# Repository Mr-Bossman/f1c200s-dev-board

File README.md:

"# f1c200s-dev-board usb otg needs to be fixed and sdcard locaton and flash pad size and 3.3 requlators pad is rotated"

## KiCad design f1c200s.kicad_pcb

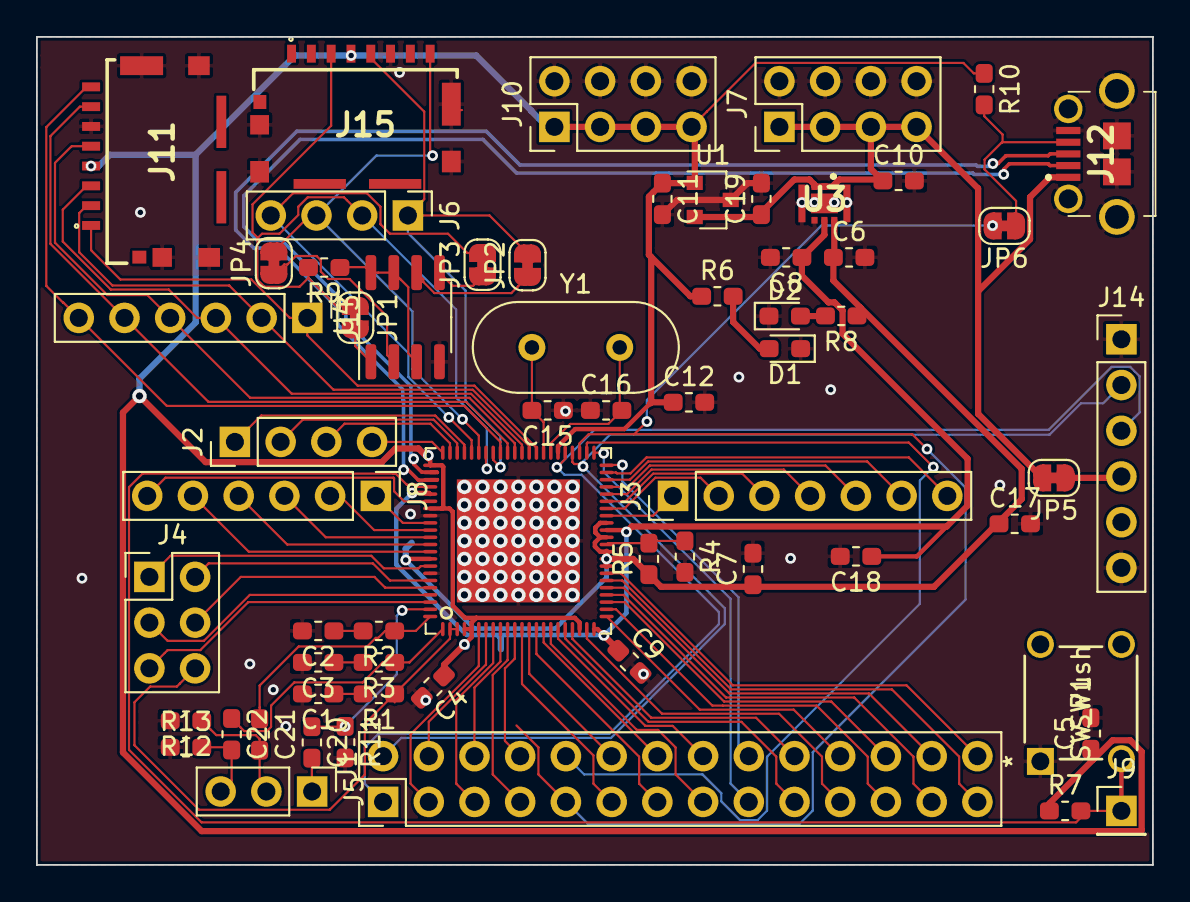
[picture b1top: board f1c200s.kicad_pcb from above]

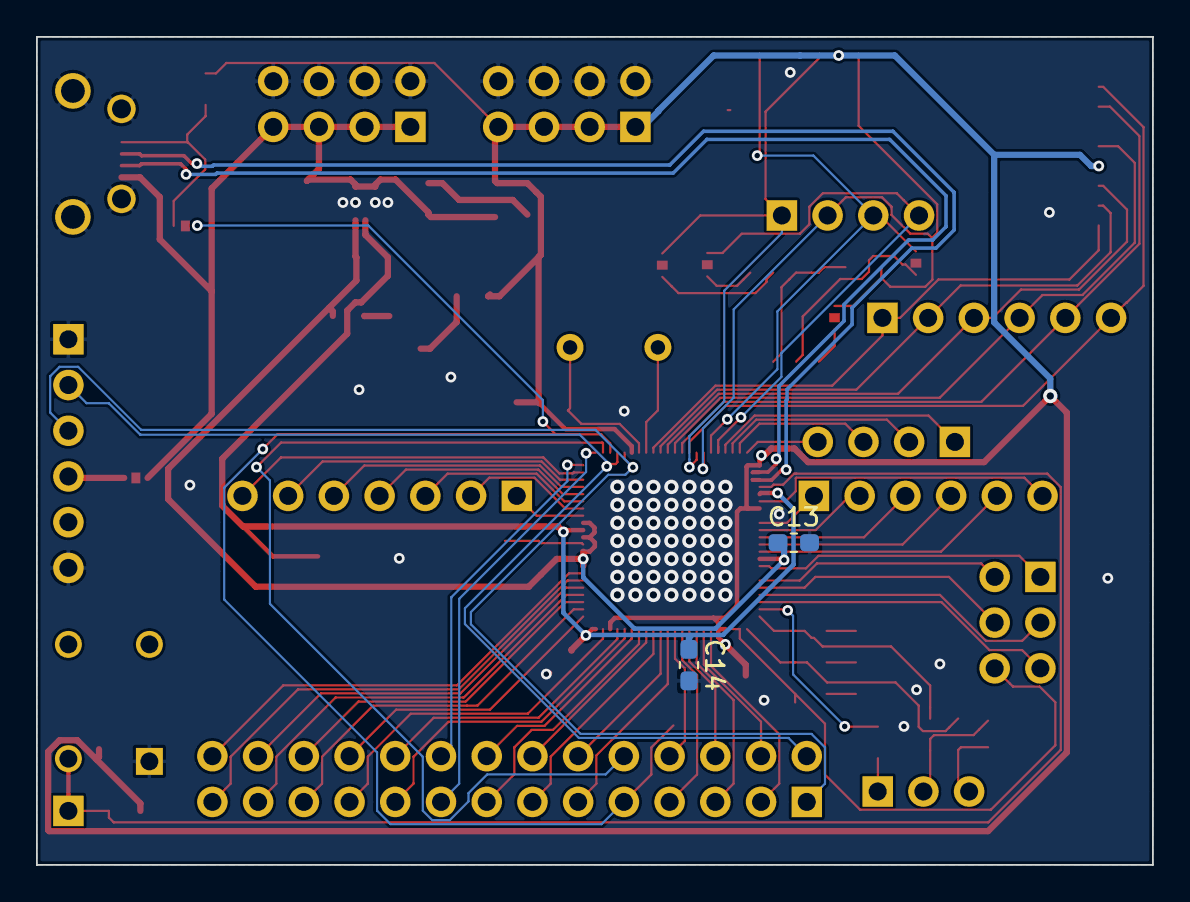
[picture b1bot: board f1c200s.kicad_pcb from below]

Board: 2 copper layers, 62.0 x 46.0 mm, 64 parts (2 on the bottom side), 89 nets.

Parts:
C1, C2, C3, C20, C21, C22: .1u; C_0603_1608Metric_Pad1.05x0.95mm_HandSolder
C4, C5, C6, C7, C8, C9, C10, C11, C12, C13, C14, C17, C18, C19: 100n; C_0603_1608Metric_Pad1.05x0.95mm_HandSolder
C15, C16: 22p; C_0603_1608Metric_Pad1.05x0.95mm_HandSolder
D1, D2: LED; LED_0603_1608Metric_Pad1.05x0.95mm_HandSolder
J1: Conn_02x14_Odd_Even; PinHeader_2x14_P2.54mm_Vertical
J2, J6: Conn_01x04_Male; PinHeader_1x04_P2.54mm_Vertical
J3: Conn_01x07_Male; PinHeader_1x07_P2.54mm_Vertical
J4: Conn_02x03_Odd_Even; PinHeader_2x03_P2.54mm_Vertical
J5: Conn_01x03_Male; PinHeader_1x03_P2.54mm_Vertical
J7, J10: Conn_02x04_Odd_Even; PinHeader_2x04_P2.54mm_Vertical
J8, J13, J14: Conn_01x06_Male; PinHeader_1x06_P2.54mm_Vertical
J9: Conn_01x01_Male; PinHeader_1x01_P2.54mm_Vertical
J11, J15: 105162-0001
J12: 10118194-0011LF; 101181940011LF
JP1: CS; SolderJumper-2_P1.3mm_Bridged_RoundedPad1.0x1.5mm
JP2: SCK; SolderJumper-2_P1.3mm_Bridged_RoundedPad1.0x1.5mm
JP3: MOSI; SolderJumper-2_P1.3mm_Bridged_RoundedPad1.0x1.5mm
JP4: MISO; SolderJumper-2_P1.3mm_Bridged_RoundedPad1.0x1.5mm
JP5, JP6: Jumper; SolderJumper-2_P1.3mm_Bridged_RoundedPad1.0x1.5mm
R1, R2, R3: 22R; C_0603_1608Metric_Pad1.05x0.95mm_HandSolder
R4, R5: 2.2K; R_0603_1608Metric_Pad1.05x0.95mm_HandSolder
R6, R8: 100; R_0603_1608Metric_Pad1.05x0.95mm_HandSolder
R7: 47K; R_0603_1608Metric_Pad1.05x0.95mm_HandSolder
R9: 3.3K; R_0603_1608Metric_Pad1.05x0.95mm_HandSolder
R10: 10k; R_0603_1608Metric_Pad1.05x0.95mm_HandSolder
R11, R12, R13: 220k; C_0603_1608Metric_Pad1.05x0.95mm_HandSolder
SW1: SW_Push; button
U1: 3.3v; SOT-23
U2: F1C100s
U3: XC6421AB03ER-G
U4: AT25xxx; SOIC-8_3.9x4.9mm_P1.27mm
Y1: 24MHz; Crystal_HC49-4H_Vertical

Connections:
+1V2: C8.1, C9.1, C14.1, C18.1, U2.22, U2.35, U2.71, U3.5
+2V5: C6.1, C7.1, C13.1, C17.1, R5.1, R8.1, U2.30, U2.31, U2.32, U2.34, U2.36, U2.80, U3.6
+3V3: C4.1, C5.1, C11.1, C12.1, J10.1, J10.3, J10.5, J10.7, J11.4, J15.4, R6.1, R7.1, R9.1, R10.1, U1.1, U2.4, U2.5, U2.20, U2.50, U2.67, U2.73, U4.3, U4.7, U4.8
+5V: C10.1, C19.1, J7.1, J7.3, J7.5, J7.7, J12.1, JP5.2, U1.2, U3.1, U3.2, U3.3
/COM: J4.6, R1.1, U2.2, U2.3
/D+: J12.3, U2.69
/D-: J12.2, U2.68
/L: C22.1, R3.1, U2.1
/LCD0: J1.1, J14.3, U2.49
/LCD1: J1.2, J14.2, U2.48
/LCD2: J1.3, U2.6
/LCD3: J1.4, U2.7
/LCD4: J1.5, U2.8
/LCD5: J1.6, U2.9
/LCD6: J1.7, U2.10
/LCD7: J1.8, U2.11
/LCD8: J1.9, JP6.2, U2.47
/LCD9: J1.10, U2.46
/LCD10: J1.11, U2.12
/LCD11: J1.12, U2.13
/LCD12: J1.13, U2.14
/LCD13: J1.14, U2.15
/LCD14: J1.15, U2.16
/LCD15: J1.16, U2.17
/LCD16: J1.17, U2.45
/LCD17: J1.18, U2.44
/LCD18: J1.19, U2.18
/LCD19: J1.20, U2.19
/LCD20: J1.21, U2.21
/LCD21: J1.22, U2.23
/LCD22: J1.23, U2.24
/LCD23: J1.24, U2.25
/LCDCLK: J1.25, U2.26
/LCDDE: J1.26, U2.27
/LCDHS: J1.27, U2.28
/LCDVS: J1.28, U2.29
/MIC: C20.1, R11.1, U2.87
/R: C21.1, R2.1, U2.88
/SDC0_CLK: J11.5, J13.4, U2.56
/SDC0_CMD: J11.3, J13.3, U2.55
/SDC0_D0: J11.7, J13.5, U2.57
/SDC0_D1: J11.8, J13.6, U2.58
/SDC0_D2: J11.1, J13.1, U2.53
/SDC0_D3: J11.2, J13.2, U2.54
/SPI_0_CLK: J6.1, J15.5, JP2.2, U2.59
/SPI_0_CS: J6.2, J15.3, JP1.1, R9.2, U2.60
/SPI_0_MISO: J6.3, J15.8, JP4.2, U2.61
/SPI_0_MOSI: J6.4, JP3.2, U2.62
GND: C1.2, C2.2, C3.2, C4.2, C5.2, C6.2, C7.2, C8.2, C9.2, C10.2, C11.2, C12.2, C13.2, C14.2, C15.1, C16.1, C17.2, C18.2, C19.2, D1.1, D2.1, J7.2, J7.4, J7.6, J7.8, J10.2, J10.4, J10.6, J10.8, J11.6, J11.10, J11.11, J11.12, J11.13, J12.5, J12.6, J12.7, J12.8, J12.9, J12.10, J12.11, J14.1, J14.6, J15.6, J15.10, J15.11, J15.12, J15.13, R4.2, R11.2, R12.2, R13.1, SW1.1, U1.3, U2.74, U2.82, U2.89, U3.4, U3.7, U3.8, U3.9, U4.4
unnamed: C1.1, R1.2
unnamed: C2.1, R2.2
unnamed: C3.1, R3.2
unnamed: C15.2, U2.52, Y1.1
unnamed: C16.2, U2.51, Y1.2
unnamed: C20.2, J5.1
unnamed: C21.2, J5.2, R12.1
unnamed: C22.2, J5.3, R13.2
unnamed: D1.2, R6.2
unnamed: D2.2, R8.2
unnamed: J2.1, U2.63
unnamed: J2.2, U2.64
unnamed: J2.3, U2.65
unnamed: J2.4, U2.66
unnamed: J3.1, U2.37
unnamed: J3.2, U2.38
unnamed: J3.3, U2.39
unnamed: J3.4, U2.40
unnamed: J3.5, U2.41
unnamed: J3.6, U2.42
unnamed: J3.7, U2.43
unnamed: J4.1, U2.81
unnamed: J4.2, U2.83
unnamed: J4.3, U2.85
unnamed: J4.4, U2.84
unnamed: J4.5, U2.86
unnamed: J8.1, U2.75
unnamed: J8.2, U2.76
unnamed: J8.3, U2.77
unnamed: J8.4, U2.78
unnamed: J8.5, U2.79
unnamed: J8.6, U2.72
unnamed: J9.1, R7.2, SW1.2, U2.70
unnamed: J12.4, JP6.1, R10.2
unnamed: J14.4, JP5.1
unnamed: JP1.2, U4.1
unnamed: JP2.1, U4.6
unnamed: JP3.1, U4.5
unnamed: JP4.1, U4.2
unnamed: R4.1, R5.2, U2.33

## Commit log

2020-08-19 rev one rev two coming soon
2020-08-24 second rev of crap board

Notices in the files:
parts and their libraries:
Copyright 2016 Accelerated Designs. All rights reserved.
